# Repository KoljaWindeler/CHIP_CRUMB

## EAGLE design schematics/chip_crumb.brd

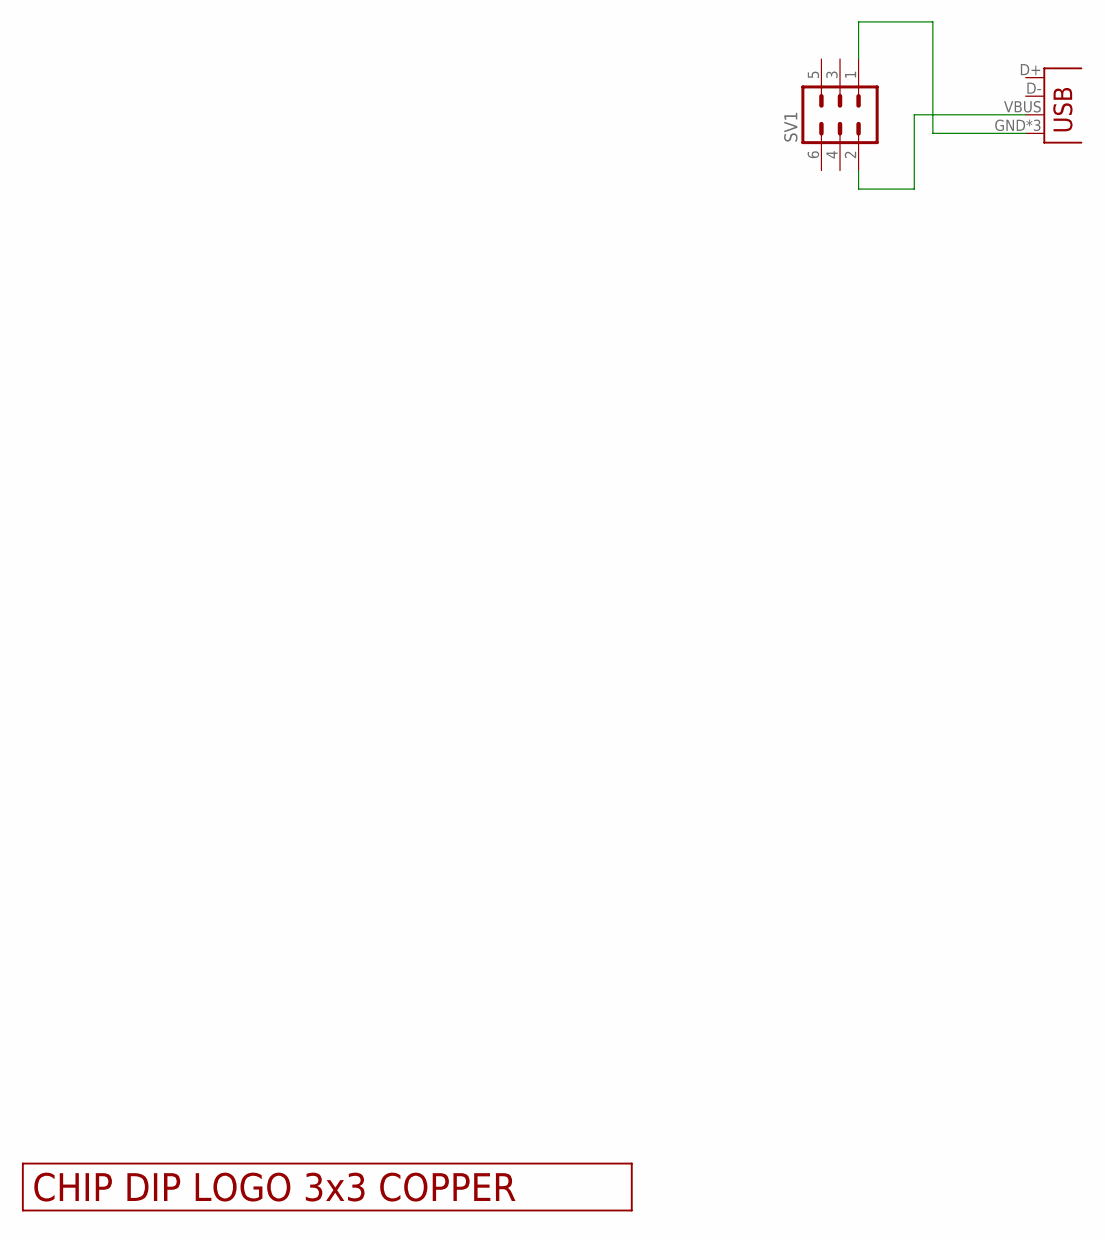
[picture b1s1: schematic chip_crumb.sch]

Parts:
SV1: MA03-2
U$4: LOGO_3X3_COPPER
USB: USBUSB-MICROB-SMT-DIP; USB-MICROB-SMT-DIP

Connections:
GND: SV1.1, USB.GND, USB.MT1 (GND), USB.MT2 (GND)
unnamed: SV1.2, USB.VBUS

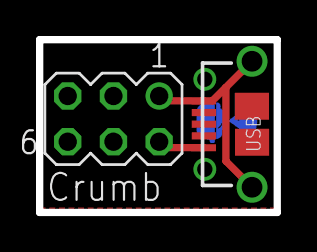
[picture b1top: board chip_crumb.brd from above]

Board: 2 copper layers, 13.2 x 9.6 mm, 3 parts (1 on the bottom side), 2 nets.

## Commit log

2016-05-03 init
